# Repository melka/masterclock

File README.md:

# masterclock

Master clock for Lepaute 30 seconds alternating pulse slave clock and possibly other models.

## background

Slave clocks are old school clocks mostly used in train stations, hospitals, factories, etc... places that needed to have accurate timekeeping and synchronized clocks in a lot of places. A master clock was responsible for keeping time and controlling all the slave clocks. There were a number of clock manufacturers, and there were a lot of way of synching the slave clocks to the master clock.

If you find a beautiful industrial slave clock, there are several options :
* Find the master clock to go with it, but you'll need space, money and time to take care of it
* Remove the old mechanical movement and replace it with a quartz one (shame on you)
* Buy one of [these](http://www.bmumford.com/clocks/driver/driver.html), but what's the fun in that ?
* Make a teeny-tiny master clock.

So here comes this project.

## goal

I got hold of two slave clocks that were salvaged from an hospital that was being destroyed in France. One of them is a Lepaute clock.

Those clocks use an alternating pulse every 30 seconds to make the minute hand advance half a minute. The pulse is ~200ms and a 1.5V battery is enough to make it go.

I wanted to make a board that could run for more than a year on a single AA battery, be highly accurate and that would be as small as possible (in this case, just enough space to fit the battery and a screw terminal to plug the clock mechanism).

That was a fail, but mostly due to firmware mistakes. Old one had flaws and kept the clock running approximately 3 1/2 weeks before draining the battery. This new version of the firmware should improve the run time dramatically. New version with new battery installed on February 27 2018 at 8:30PM, let's see how long it'll run...

When all the chips are sleeping, my multimeter shows nothing, and the wake-up time is so short that I can't measure it precisely. I've gotten a [uCurrent Gold](https://www.eevblog.com/projects/ucurrent/), so I can measure some current consumptions, but I'm running into problems getting it to work with my oscilloscope. I'll update with curves and graphes when possible.

## BOM

Full BOM can be found on [mouser](https://www.mouser.fr/ProjectManager/ProjectDetail.aspx?AccessID=3831f781b1)

* [TPS60313](http://www.ti.com/product/TPS60313) : Charge Pump
* [MSP430G2553](http://www.ti.com/product/MSP430G2553) : MCU
* [DS3231SN](https://www.maximintegrated.com/en/products/digital/real-time-clocks/DS3231.html) : I2C RTC
* [DRV8838](http://www.ti.com/product/DRV8838) : Brushed DC Motor Driver

## circuit

Power is provided by a single AA battery.

A TPS60313 converts this voltage to 3V in order to power the MCU and RTC. Input voltage can go as low as 0.9V in order to get 3V output. Quiescent current at no-load is 35uA.

MCU is an MSP430G2553 spending most of its time in LPM4 (consumption should be about 0.15uA). uCurrent shows around 0.105uA.

RTC is a DS3231SN, powered only via VBAT to reduce the current consumption of the device. According to the datasheet, Ibatt goes up to 70uA when active, while Ivcc goes up to 200uA. Ibatt when only timekeeping is 0.84uA typical. Measuring with a uCurrent gold shows this number to be accurate.
A DS3231M could be used, but the SN is a tad bit more accurate (+/-2PPM against +/-5PPM for the M).

To drive the mechanism, an alternating pulse is necessary. This could be done with a discrete H-bridge, but I opted for a DRV8838, directly powered from an MCU pin. This way, the DRV isn't even sleeping, but only switched on when needed, once every 30 seconds. Vmotor comes directly from the AA battery.

## on soldering

This board being an exercise in miniaturisation, all the resistors and caps are 0402... I advise you not to try to solder this board without a good-ish soldering iron and an hot air gun. I'm using one of the cheap chinese all-in-one stations, but without hot air, some components are next to impossible, especially the DRV8838.

## firmware

Firmware was developed using TI's Cloud IDE since I'm using a Mac and it was the simplest solution.

New version of the firmware configures the RTC to ring 2 alarms : one every time the time goes past HH:MM:00s, the other every time the time goes past HH:MM:30s. The RTC will pull low the interrupt pin 8ms every 30 seconds. Power consumption when the pin is high is microscopic, but it goes up when pulled low. The old firmware was generating a 1Hz square wave with a 50% duty cycle, so the higher current consumption was happening 50% of the time. Now, it should happen only 16ms / minute or 0.00027% of the time...

Old version for information purpose :

```
On boot, the MSP430 runs at 1MHZ and sets some configuration on the RTC :
 * Enable Oscillator
 * Battery-Backed Square-Wave Enable allows the interrupt to be sent when powered by VBAT
 * Rate Select set to 1Hz
 * Interrupt Control set to Square-Wave
 * Disable Alarms
```

P1.4 of the MSP430 is set as an interrupt pin, and then it is put to sleep with external interrupts enabled (LPM4 + GIE).

Every 30 seconds, the RTC pulls P1.4 low, which wakes up the MSP430. We start by clearing the alarm flags of the RTC. A var to keep the inversion of the phase pin is used to check if we should pull P1.1 high or low and inverted each time. We can then proceed to send the enable signal to the DRV8838 so that we advance the needle one step.

MSP430 current consumption while in LPM4 is around 105nA, and 370uA when awaken. The old firmware was waking it up every second for a couple cycles, and then for a full 200ms while sending the pulse every second. Now, we only wake up the MSP430 every 30 seconds for the full 200ms. The old firmware was also toggling the state of P1.1 every 30 seconds, so it was staying high for a full 30 seconds before being toggled low. Now, it's only pulled high if necessary.

Old version for information purpose :

```
Each second, the RTC sends a pulse on P1.4, which wakes up the MSP430. A counter is incremented and when this seconds counter == 30, power is applied to the DRV8838 by putting P1.0 high (DRV_VCC), pulse direction is reversed by toggling P1.1 (DRV_PH) and a 200ms pulse is sent via P1.2 (DRV_EN). Counter is reset and the MSP430 goes back to sleep.
```

### references
 * [Horloge Mère (in French)](http://f5mna.free.fr/h_mere.htm)
 * [Powering an MSP430 From a Single Battery Cell](http://www.ti.com/lit/an/slaa398/slaa398.pdf)

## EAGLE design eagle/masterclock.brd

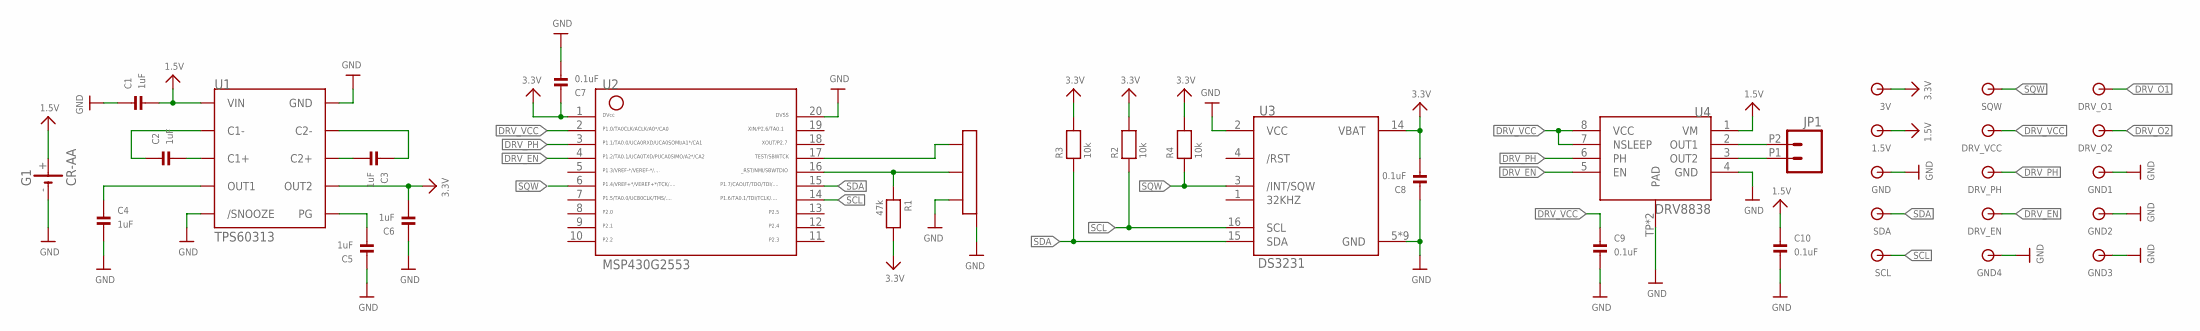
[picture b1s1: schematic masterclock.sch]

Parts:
1.5V, 3V: TESTPAD
C1, C2, C3, C4, C5, C6: 1uF; 0402
C7, C8, C9, C10: 0.1uF; 0402
DRV_EN: TESTPAD
DRV_O1, DRV_O2: TESTPAD
DRV_PH: TESTPAD
DRV_VCC: TESTPAD
G1: CR-AA; CRAA
GND: TESTPAD
GND1, GND2, GND3, GND4: GND; TESTPAD
JP1: M022.54MM_SCREWTERM; 1X02_2.54_SCREWTERM
R1: 47k; 0402
R2, R3, R4: 10k; 0402
SCL: TESTPAD
SDA: TESTPAD
SQW: TESTPAD
U1: TPS60313; MSOP10
U2: MSP430G2553; PW20
U3: DS3231; SO16
U4: DRV8838; WSON8
U$27: M03; TE-MICRO-MNL-

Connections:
1.5V: 1.5V.P$1, C1.2, C10.1, G1.+, U1.P$3 (VIN), U4.1 (VM)
3.3V: 3V.P$1, C6.2, C7.1, C8.2, R1.2, R2.2, R3.2, R4.2, U1.P$6 (OUT2), U2.1, U3.14 (VBAT)
/RST: R1.1, U2.16, U$27.P$2
DRV_EN: DRV_EN.P$1, U2.4, U4.5 (EN)
DRV_O1: DRV_O1.P$1, JP1.P2 (2), U4.2 (OUT1)
DRV_O2: DRV_O2.P$1, JP1.P1 (1), U4.3 (OUT2)
DRV_PH: DRV_PH.P$1, U2.3, U4.6 (PH)
DRV_VCC: C9.1, DRV_VCC.P$1, U2.2, U4.7 (NSLEEP), U4.8 (VCC)
GND: C1.1, C4.2, C5.1, C6.1, C7.2, C8.1, C9.2, C10.2, G1.-, GND.P$1, GND1.P$1, GND2.P$1, GND3.P$1, GND4.P$1, U1.P$1 (/SNOOZE), U1.P$9 (GND), U2.20, U3.2 (VCC), U3.5 (GND), U3.6 (GND), U3.7 (GND), U3.8 (GND), U3.9 (GND), U3.10 (GND), U3.11 (GND), U3.12 (GND), U3.13 (GND), U4.4 (GND), U4.TP (PAD), U4.TP1 (PAD), U$27.H1, U$27.H2, U$27.P$3
unnamed: C2.2, U1.P$4 (C1+)
unnamed: C2.1, U1.P$2 (C1-)
unnamed: C3.1, U1.P$8 (C2-)
unnamed: C3.2, U1.P$7 (C2+)
unnamed: C5.2, U1.P$10 (PG)
PWROUT: C4.1, U1.P$5 (OUT1)
SCL: R2.1, SCL.P$1, U2.14, U3.16 (SCL)
SDA: R3.1, SDA.P$1, U2.15, U3.15 (SDA)
SQW: R4.1, SQW.P$1, U2.6, U3.3 (/INT/SQW)
TEST: U2.17, U$27.P$1

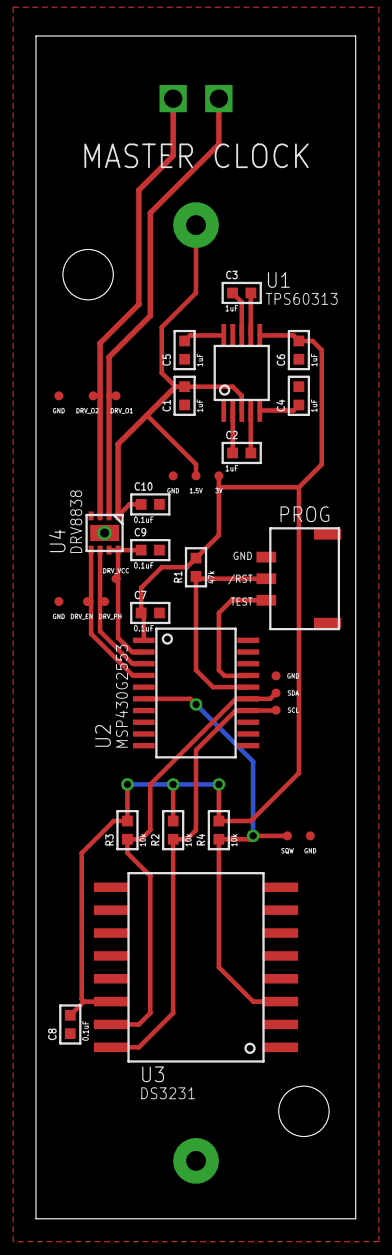
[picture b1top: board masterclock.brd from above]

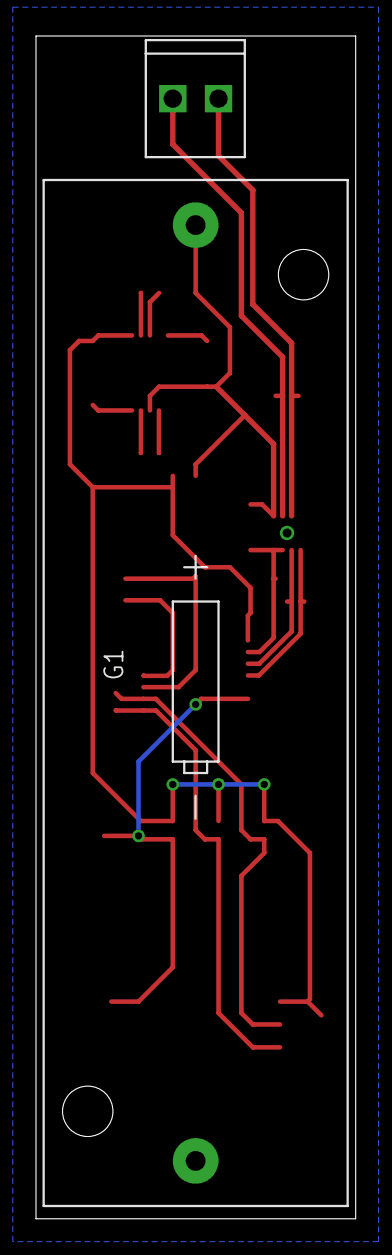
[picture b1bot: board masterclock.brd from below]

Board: 2 copper layers, 17.8 x 65.7 mm, 36 parts (2 on the bottom side), 19 nets.

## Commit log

2018-02-27 New firmware version
    Lots of new stuff
